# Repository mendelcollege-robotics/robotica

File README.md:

# About
This is the repository for all the files associated with, and used to create, a soccer robot for participation in the [Robocup](https://www.robocup.org/leagues/18). Made by students of the Mendelcollege, from team 'Mendel'.

# Info:

  [Mendelcollege.nl](https://mendelcollege.nl/ontdek-je-talenten/robotica-en-beta/)

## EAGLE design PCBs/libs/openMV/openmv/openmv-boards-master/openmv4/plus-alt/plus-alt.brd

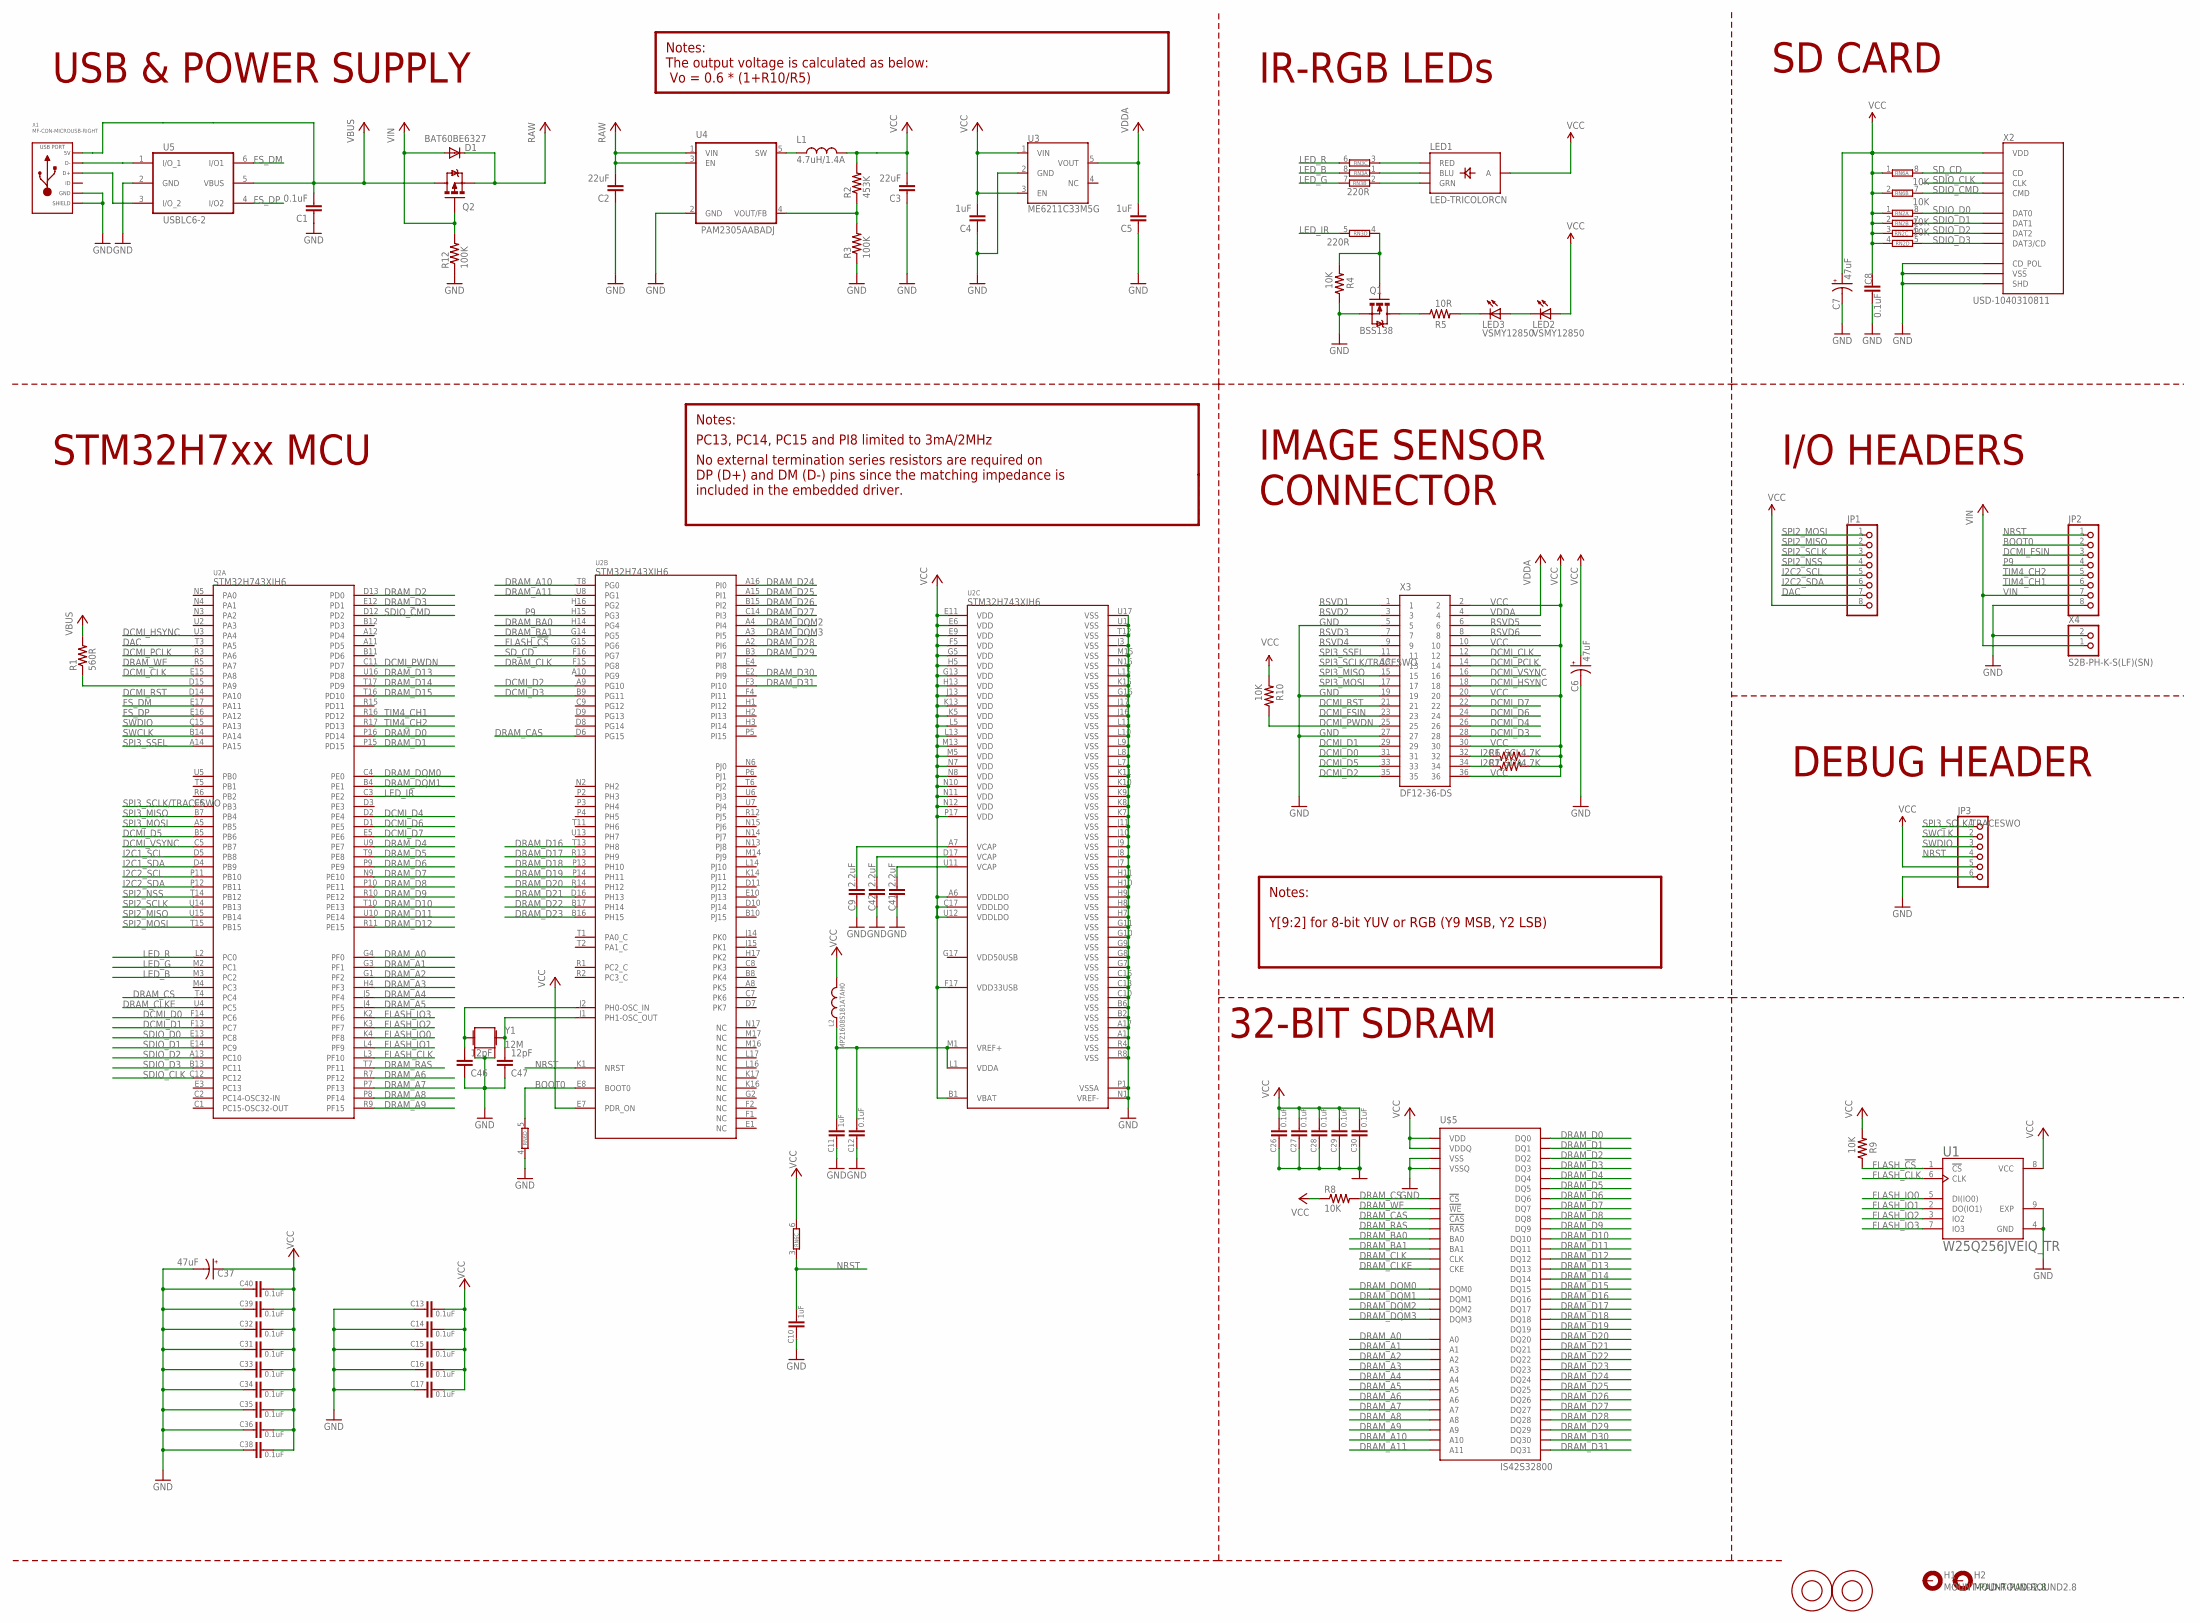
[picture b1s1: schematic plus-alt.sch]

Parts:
C1, C8, C12, C13, C14, C15, C16, C17, C26, C27, C28, C29, C30, C31, C32, C33, C34, C35, C36, C38, C39, C40: 0.1uF; 0402-CAP
C2, C3: 22uF; 0805
C4, C5, C10, C11: 1uF; 0402-CAP
C6, C7, C37: 47uF; EIA3216
C9, C41, C42: 2.2uF; 0402-CAP
C46, C47: 12pF; 0402-CAP
D1: BAT60BE6327; SOD-323
H1, H2: MOUNT-PAD-ROUND2.8; 2,8-PAD
JP1, JP2: PINHD-1X8; 1X08
JP3: PINHD-1X6; 1X06
L1: 4.7uH/1.4A; 1007
L2: MPZ1608S181ATAH0; C0402
LED1: LED-TRICOLORCN; LED-TRICOLOR-SMD
LED2, LED3: VSMY12850; LED-1206
M1, M2: 9774030243R; 9774030151R
Q1: BSS138; SOT23-3
Q2: AO3401; SOT23-3
R1: 560R; 0402-RES
R2: 453K; 0402-RES
R3, R12: 100K; 0402-RES
R4, R8, R9, R10: 10K; 0402-RES
R5: 10R; 0402-RES
R6, R7: 4.7K; 0402-RES
RN2, RN6: 10K; EXBV8V
RN3: 220R; EXBV8V
U1: W25Q256JVEIQ_TR; SON127P800X600X80-9N
U2: *; TFBGA240+25
U3: ME6211C33M5G; SOT23-5
U4: PAM2305AABADJ; TSOT25
U5: USBLC6-2; SOT-23-6L
U$5: IS42S32800; BGA90
X1: MF-CON-MICROUSB-RIGHT; MICROUSB-RIGHT
X2: USD-1040310811; 1040310811
X3: DF12-36-DS
X4: S2B-PH-K-S(LF)(SN); JST-PH-2-THM-RA
Y1: 12M; CRYSTAL-2.5X2.0

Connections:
BOOT0: JP2.2, RN6.5 (2), U2.E8 (BOOT0)
DAC: JP1.7, U2.T3 (PA5)
DCMI_CLK: U2.E15 (PA8), X3.12
DCMI_D0: U2.F14 (PC6), X3.31
DCMI_D1: U2.F13 (PC7), X3.29
DCMI_D2: U2.A9 (PG10), X3.35
DCMI_D3: U2.B9 (PG11), X3.28
DCMI_D4: U2.D2 (PE4), X3.26
DCMI_D5: U2.B5 (PB6), X3.33
DCMI_D6: U2.D1 (PE5), X3.24
DCMI_D7: U2.E5 (PE6), X3.22
DCMI_FSIN: JP2.3, X3.23
DCMI_HSYNC: U2.U3 (PA4), X3.18
DCMI_PCLK: U2.R3 (PA6), X3.14
DCMI_PWDN: R10.1, U2.C11 (PD7), X3.25
DCMI_RST: U2.D14 (PA10), X3.21
DCMI_VSYNC: U2.C5 (PB7), X3.16
DRAM_A0: U2.G4 (PF0), U$5.G8 (A0)
DRAM_A1: U2.G3 (PF1), U$5.G9 (A1)
DRAM_A2: U2.G1 (PF2), U$5.F7 (A2)
DRAM_A3: U2.H4 (PF3), U$5.F3 (A3)
DRAM_A4: U2.J5 (PF4), U$5.G1 (A4)
DRAM_A5: U2.J4 (PF5), U$5.G2 (A5)
DRAM_A6: U2.R7 (PF12), U$5.G3 (A6)
DRAM_A7: U2.P7 (PF13), U$5.H1 (A7)
DRAM_A8: U2.P8 (PF14), U$5.H2 (A8)
DRAM_A9: U2.R9 (PF15), U$5.J3 (A9)
DRAM_A10: U2.T8 (PG0), U$5.G7 (A10)
DRAM_A11: U2.U8 (PG1), U$5.H9 (A11)
DRAM_BA0: U2.H14 (PG4), U$5.J7 (BA0)
DRAM_BA1: U2.G14 (PG5), U$5.H8 (BA1)
DRAM_CAS: U2.D6 (PG15), U$5.K7 (!CAS)
DRAM_CLK: U2.F15 (PG8), U$5.J1 (CLK)
DRAM_CLKE: U2.U4 (PC5), U$5.J2 (CKE)
DRAM_CS: R8.2, U2.T4 (PC4), U$5.J8 (!CS)
DRAM_D0: U2.P16 (PD14), U$5.R8 (DQ0)
DRAM_D1: U2.P15 (PD15), U$5.N7 (DQ1)
DRAM_D2: U2.D13 (PD0), U$5.R9 (DQ2)
DRAM_D3: U2.E12 (PD1), U$5.N8 (DQ3)
DRAM_D4: U2.U9 (PE7), U$5.P9 (DQ4)
DRAM_D5: U2.T9 (PE8), U$5.M8 (DQ5)
DRAM_D6: U2.P9 (PE9), U$5.M7 (DQ6)
DRAM_D7: U2.N9 (PE10), U$5.L8 (DQ7)
DRAM_D8: U2.P10 (PE11), U$5.L2 (DQ8)
DRAM_D9: U2.R10 (PE12), U$5.M3 (DQ9)
DRAM_D10: U2.T10 (PE13), U$5.M2 (DQ10)
DRAM_D11: U2.U10 (PE14), U$5.P1 (DQ11)
DRAM_D12: U2.R11 (PE15), U$5.N2 (DQ12)
DRAM_D13: U2.U16 (PD8), U$5.R1 (DQ13)
DRAM_D14: U2.T17 (PD9), U$5.N3 (DQ14)
DRAM_D15: U2.T16 (PD10), U$5.R2 (DQ15)
DRAM_D16: U2.T13 (PH8), U$5.E8 (DQ16)
DRAM_D17: U2.R13 (PH9), U$5.D7 (DQ17)
DRAM_D18: U2.P13 (PH10), U$5.D8 (DQ18)
DRAM_D19: U2.P14 (PH11), U$5.B9 (DQ19)
DRAM_D20: U2.R14 (PH12), U$5.C8 (DQ20)
DRAM_D21: U2.D16 (PH13), U$5.A9 (DQ21)
DRAM_D22: U2.B17 (PH14), U$5.C7 (DQ22)
DRAM_D23: U2.B16 (PH15), U$5.A8 (DQ23)
DRAM_D24: U2.A16 (PI0), U$5.A2 (DQ24)
DRAM_D25: U2.A15 (PI1), U$5.C3 (DQ25)
DRAM_D26: U2.B15 (PI2), U$5.A1 (DQ26)
DRAM_D27: U2.C14 (PI3), U$5.C2 (DQ27)
DRAM_D28: U2.A2 (PI6), U$5.B1 (DQ28)
DRAM_D29: U2.B3 (PI7), U$5.D2 (DQ29)
DRAM_D30: U2.E2 (PI9), U$5.D3 (DQ30)
DRAM_D31: U2.F3 (PI10), U$5.E2 (DQ31)
DRAM_DQM0: U2.C4 (PE0), U$5.K9 (DQM0)
DRAM_DQM1: U2.B4 (PE1), U$5.K1 (DQM1)
DRAM_DQM2: U2.A4 (PI4), U$5.F8 (DQM2)
DRAM_DQM3: U2.A3 (PI5), U$5.F2 (DQM3)
DRAM_RAS: U2.T7 (PF11), U$5.J9 (!RAS)
DRAM_WE: U2.R5 (PA7), U$5.K8 (!WE)
FLASH_!CS: R9.1, U1.1 (!CS), U2.G15 (PG6)
FLASH_CLK: U1.6 (CLK), U2.L3 (PF10)
FLASH_IO0: U1.5 (DI(IO0)), U2.K4 (PF8)
FLASH_IO1: U1.2 (DO(IO1)), U2.L4 (PF9)
FLASH_IO2: U1.3 (IO2), U2.K3 (PF7)
FLASH_IO3: U1.7 (IO3), U2.K2 (PF6)
FS_DM: U2.E17 (PA11), U5.6 (I/O1)
FS_DP: U2.E16 (PA12), U5.4 (I/O2)
GND: C1.1, C2.1, C3.1, C4.1, C5.1, C6.C (-), C7.C (-), C8.2, C9.2, C10.2, C11.2, C12.2, C13.2, C14.2, C15.2, C16.2, C17.2, C26.2, C27.2, C28.2, C29.2, C30.2, C31.2, C32.2, C33.2, C34.2, C35.2, C36.2, C37.C (-), C38.2, C39.2, C40.2, C41.2, C42.2, C46.1, C47.1, JP2.8, JP3.6, Q1.2 (S), R3.1, R4.1, R12.1, RN6.4 (1), U1.4 (GND), U1.9 (EXP), U2.A1 (VSS), U2.A17 (VSS), U2.B2 (VSS), U2.B6 (VSS), U2.C10 (VSS), U2.C13 (VSS), U2.C16 (VSS), U2.G7 (VSS), U2.G8 (VSS), U2.G9 (VSS), U2.G10 (VSS), U2.G11 (VSS), U2.G16 (VSS), U2.H7 (VSS), U2.H8 (VSS), U2.H9 (VSS), U2.H10 (VSS), U2.H11 (VSS), U2.J3 (VSS), U2.J7 (VSS), U2.J8 (VSS), U2.J9 (VSS), U2.J10 (VSS), U2.J11 (VSS), U2.J16 (VSS), U2.J17 (VSS), U2.K7 (VSS), U2.K8 (VSS), U2.K9 (VSS), U2.K10 (VSS), U2.K11 (VSS), U2.K15 (VSS), U2.L7 (VSS), U2.L8 (VSS), U2.L9 (VSS), U2.L10 (VSS), U2.L11 (VSS), U2.L15 (VSS), U2.M15 (VSS), U2.N1 (VREF-), U2.N16 (VSS), U2.P1 (VSSA), U2.R4 (VSS), U2.R8 (VSS), U2.T12 (VSS), U2.U1 (VSS), U2.U17 (VSS), U3.2 (GND), U4.2 (GND), U5.2 (GND), U$5.A3 (VSS), U$5.B3 (VSSQ), U$5.B8 (VSSQ), U$5.C1 (VSSQ), U$5.D1 (VSSQ), U$5.E9 (VSSQ), U$5.F1 (VSS), U$5.L3 (VSS), U$5.L9 (VSSQ), U$5.M1 (VSSQ), U$5.N1 (VSSQ), U$5.P3 (VSSQ), U$5.P8 (VSSQ), U$5.R3 (VSS), X1.5 (GND), X1.S1 (SLD), X1.S2 (SLD), X1.S3 (SLD), X1.S4 (SLD), X1.S5 (SLD), X1.S6 (SLD), X2.CD$2 (CD_POL), X2.G$1 (SHD), X2.G$2 (SHD), X2.G$3 (SHD), X2.G$4 (SHD), X2.P$6 (VSS), X3.5, X3.19, X3.27, X4.2 (1), Y1.2, Y1.4
I2C1_SCL: R6.2, U2.D5 (PB8), X3.32
I2C1_SDA: R7.2, U2.D4 (PB9), X3.34
I2C2_SCL: JP1.5, U2.P11 (PB10)
I2C2_SDA: JP1.6, U2.P12 (PB11)
LED_B: RN3.8 (2), U2.M3 (PC2)
LED_G: RN3.7 (2), U2.M2 (PC1)
LED_IR: RN3.5 (2), U2.C3 (PE2)
LED_R: RN3.6 (2), U2.L2 (PC0)
unnamed: U5.1 (I/O_1), X1.2 (D-)
unnamed: U5.3 (I/O_2), X1.3 (D+)
unnamed: Q1.1 (G), R4.2, RN3.4 (1)
unnamed: LED1.B (BLU), RN3.1
unnamed: LED1.R (RED), RN3.3 (1)
unnamed: LED1.G (GRN), RN3.2 (1)
unnamed: LED3.C, R5.2
unnamed: R2.1, R3.2, U4.4 (VOUT/FB)
unnamed: Q1.3 (D), R5.1
unnamed: LED2.C, LED3.A
unnamed: C11.1, C12.1, L2.1, U2.L1 (VDDA), U2.M1 (VREF+)
unnamed: R1.1, U2.D15 (PA9)
unnamed: C46.2, U2.J2 (PH0-OSC_IN), Y1.3 (2)
unnamed: C47.2, U2.J1 (PH1-OSC_OUT), Y1.1
NRST: C10.1, JP2.1, JP3.4, RN6.3 (1), U2.K1 (NRST)
P9: JP2.4, U2.H15 (PG3)
RAW: C2.2, D1.1 (C), Q2.2 (S), U4.1 (VIN), U4.3 (EN)
RSVD1: X3.1
RSVD2: X3.3
RSVD3: X3.7
RSVD4: X3.9
RSVD5: X3.6
RSVD6: X3.8
SDIO_CLK: U2.C12, X2.P$5 (CLK)
SDIO_CMD: RN6.7 (2), U2.D12 (PD2), X2.P$3 (CMD)
SDIO_D0: RN2.8 (2), U2.E13 (PC8), X2.P$7 (DAT0)
SDIO_D1: RN2.7 (2), U2.E14 (PC9), X2.P$8 (DAT1)
SDIO_D2: RN2.6 (2), U2.A13 (PC10), X2.P$1 (DAT2)
SDIO_D3: RN2.5 (2), U2.B13 (PC11), X2.P$2 (DAT3/CD)
SD_CD: RN6.8 (2), U2.F16 (PG7), X2.CD$1 (CD)
SPI2_MISO: JP1.2, U2.U15 (PB14)
SPI2_MOSI: JP1.1, U2.T15 (PB15)
SPI2_NSS: JP1.4, U2.T14 (PB12)
SPI2_SCLK: JP1.3, U2.U14 (PB13)
SPI3_MISO: U2.B7 (PB4), X3.15
SPI3_MOSI: U2.A5 (PB5), X3.17
SPI3_SCLK/TRACESWO: JP3.1, U2.C6 (PB3), X3.13
SPI3_SSEL: U2.A14 (PA15), X3.11
SW: L1.1, U4.5 (SW)
SWCLK: JP3.2, U2.B14 (PA14)
SWDIO: JP3.3, U2.C15 (PA13)
TIM4_CH1: JP2.6, U2.R16 (PD12)
TIM4_CH2: JP2.5, U2.R17 (PD13)
VBUS: C1.2, Q2.3 (D), R1.2, U5.5 (VBUS), X1.1 (5V)
VCAP1: C9.1, U2.A7 (VCAP)
VCAP3: C41.1, U2.U11 (VCAP)
VCAP4: C42.1, U2.D17 (VCAP)
VCC: C3.2, C4.2, C6.A (+), C7.A (+), C8.1, C13.1, C14.1, C15.1, C16.1, C17.1, C26.1, C27.1, C28.1, C29.1, C30.1, C31.1, C32.1, C33.1, C34.1, C35.1, C36.1, C37.A (+), C38.1, C39.1, C40.1, JP1.8, JP3.5, L1.2, L2.2, LED1.V (A), LED2.A, R2.2, R6.1, R7.1, R8.1, R9.2, R10.2, RN2.1, RN2.2 (1), RN2.3 (1), RN2.4 (1), RN6.1, RN6.2 (1), RN6.6 (2), U1.8 (VCC), U2.A6 (VDDLDO), U2.B1 (VBAT), U2.C17 (VDDLDO), U2.E6 (VDD), U2.E7 (PDR_ON), U2.E9 (VDD), U2.E11 (VDD), U2.F5 (VDD), U2.F17 (VDD33USB), U2.G5 (VDD), U2.G13 (VDD), U2.H5 (VDD), U2.H13 (VDD), U2.J13 (VDD), U2.K5 (VDD), U2.K13 (VDD), U2.L5 (VDD), U2.L13 (VDD), U2.M5 (VDD), U2.M13 (VDD), U2.N7 (VDD), U2.N8 (VDD), U2.N10 (VDD), U2.N11 (VDD), U2.N12 (VDD), U2.P17 (VDD), U2.U12 (VDDLDO), U3.1 (VIN), U3.3 (EN), U$5.A7 (VDD), U$5.B2 (VDDQ), U$5.B7 (VDDQ), U$5.C9 (VDDQ), U$5.D9 (VDDQ), U$5.E1 (VDDQ), U$5.F9 (VDD), U$5.L1 (VDDQ), U$5.L7 (VDD), U$5.M9 (VDDQ), U$5.N9 (VDDQ), U$5.P2 (VDDQ), U$5.P7 (VDDQ), U$5.R7 (VDD), X2.P$4 (VDD), X3.2, X3.10, X3.20, X3.30, X3.36
VDDA: C5.2, U3.5 (VOUT), X3.4
VIN: D1.2 (A), JP2.7, Q2.1 (G), R12.2, X4.1 (2)

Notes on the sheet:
PC13, PC14, PC15 and PI8 limited to 3mA/2MHz
SD CARD
Y[9:2] for 8-bit YUV or RGB (Y9 MSB, Y2 LSB)
Notes:
IMAGE SENSOR CONNECTOR
STM32H7xx MCU
IR-RGB LEDs
USB & POWER SUPPLY
DEBUG HEADER
I/O HEADERS
No external termination series resistors are required on DP (D+) and DM (D-) pins since the matching impedance is included in the embedded driver.
The output voltage is calculated as below: Vo = 0.6 * (1+R10/R5)
32-BIT SDRAM

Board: 6 copper layers, 80 parts (25 on the bottom side), 134 nets, no tracks yet.

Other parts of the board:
U$1: WEEE
U$2: ROHS
U$3: OMV-LOGO
U$4: OMV-LOGO-SMALL

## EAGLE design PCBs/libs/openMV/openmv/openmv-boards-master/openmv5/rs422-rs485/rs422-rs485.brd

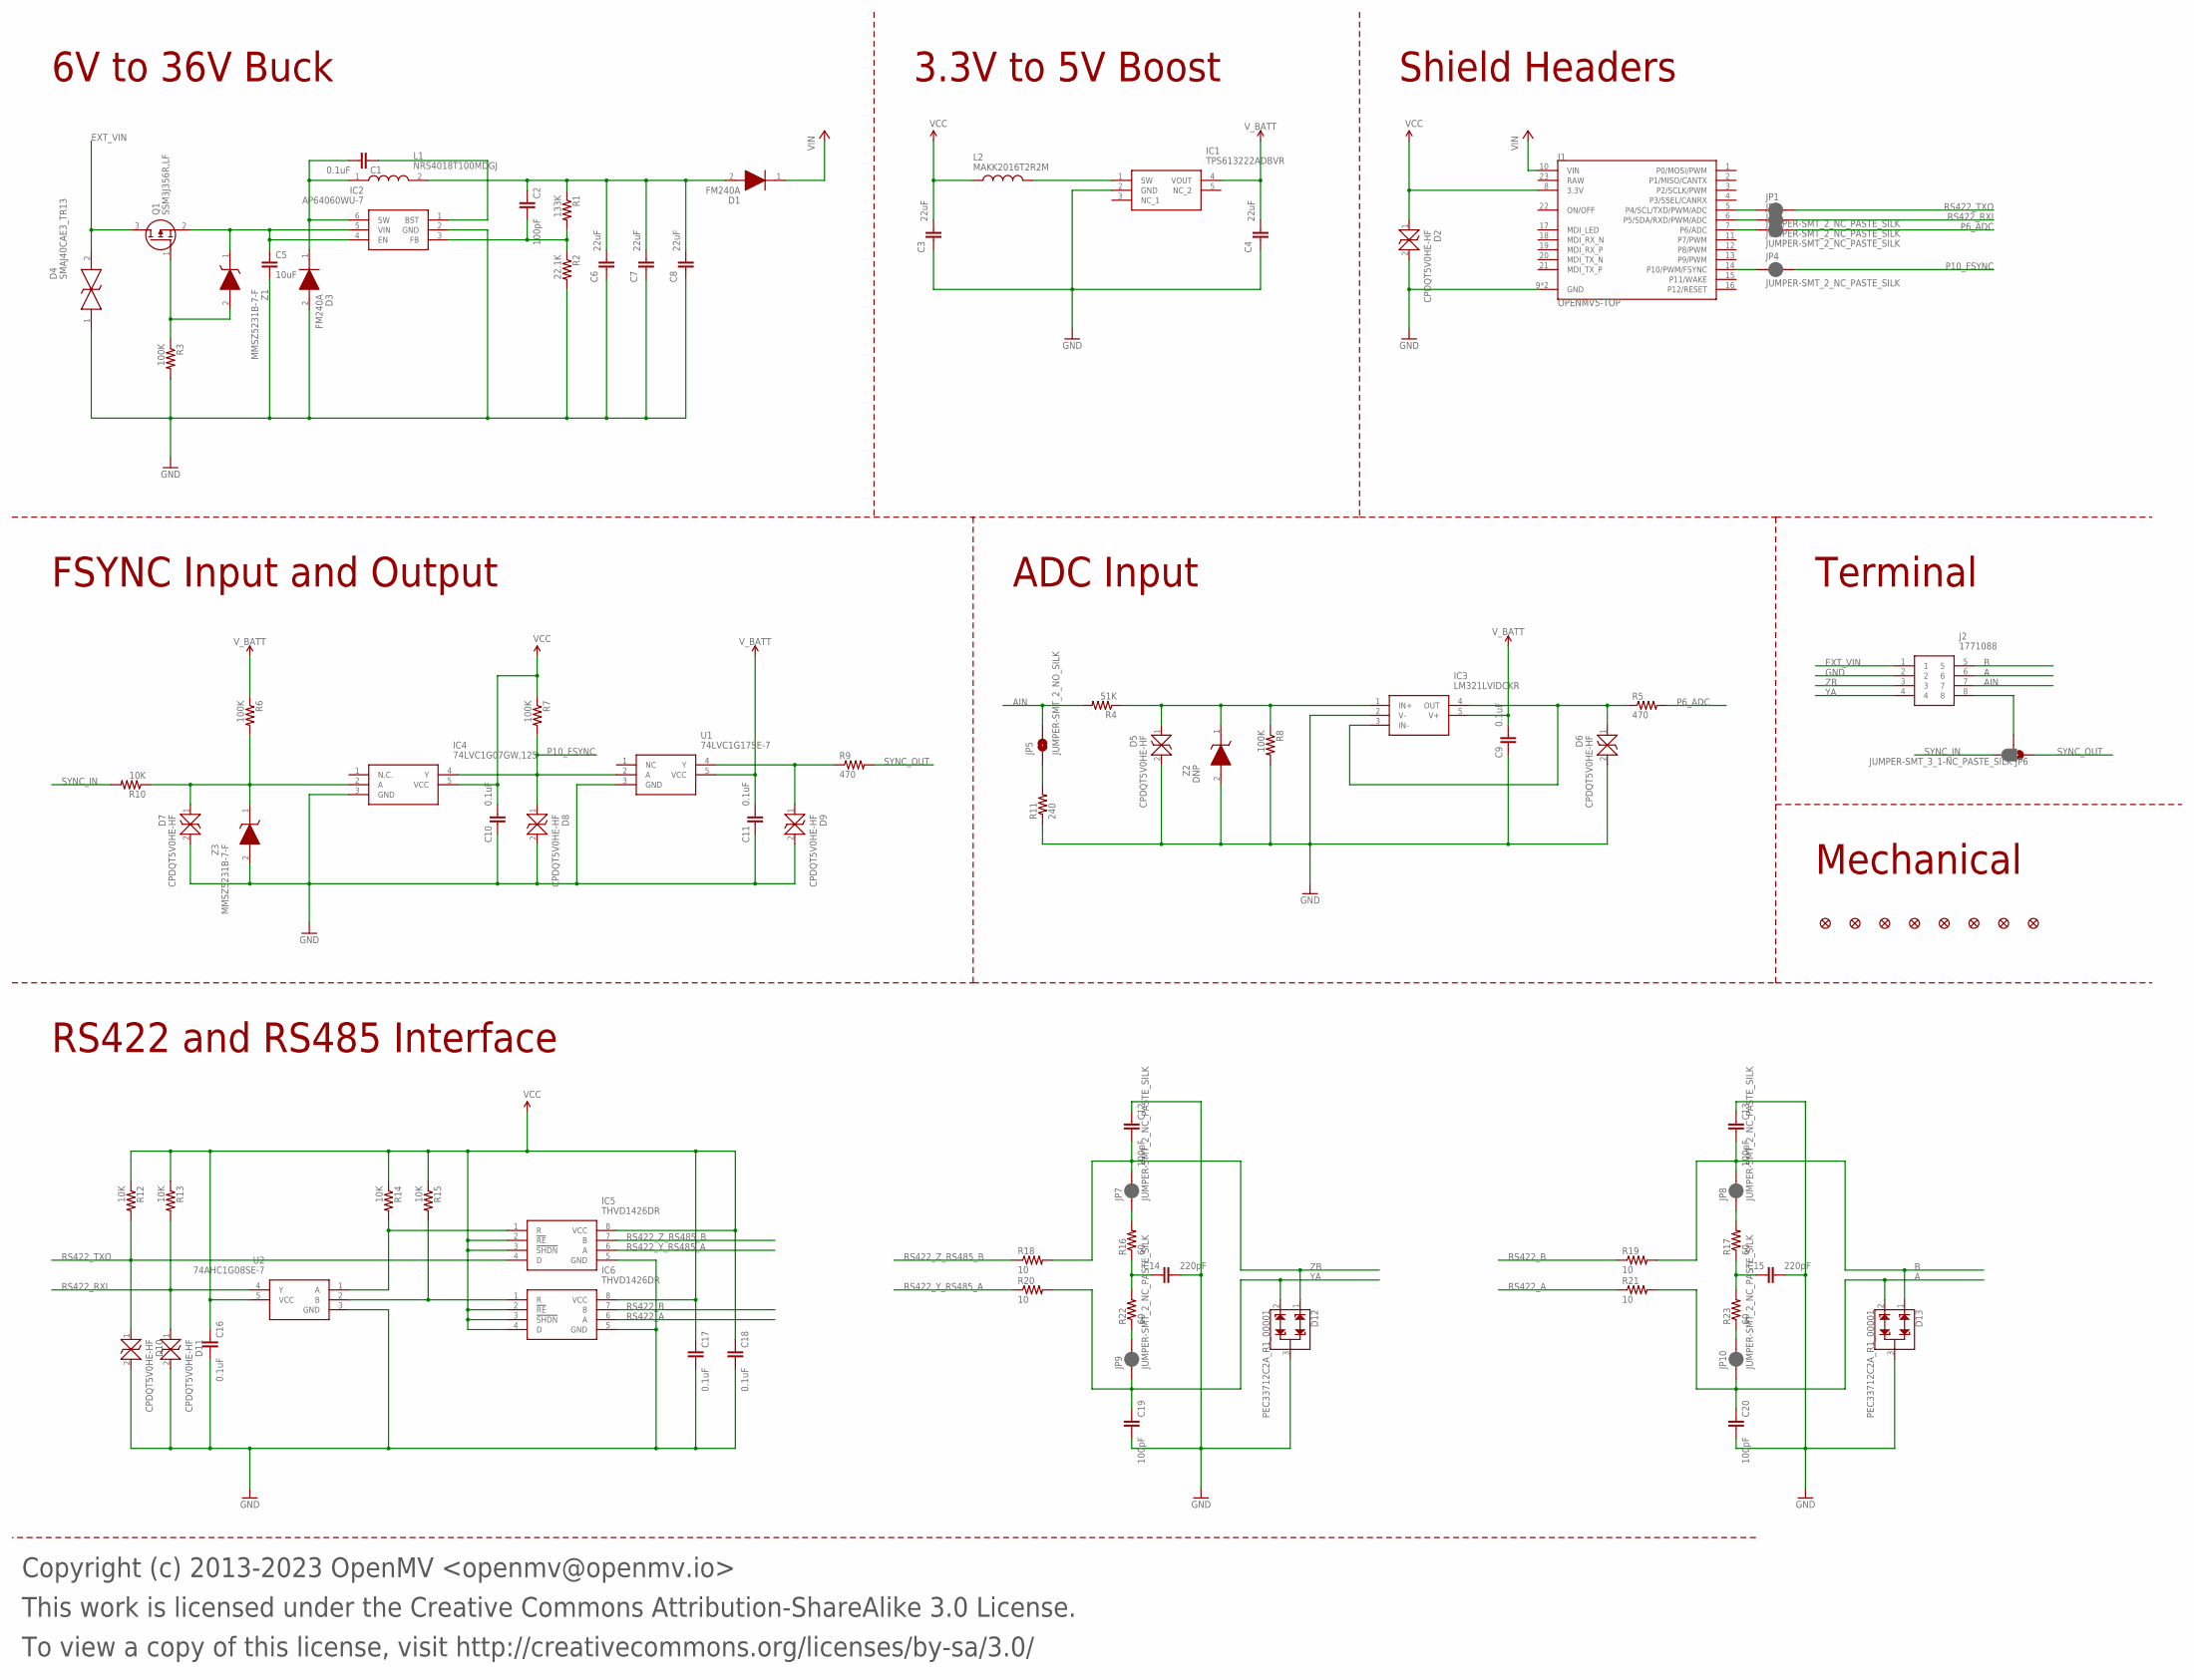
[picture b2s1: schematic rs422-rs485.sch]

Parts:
C1, C9, C10, C11, C16, C17, C18: 0.1uF; 0402-CAP; MPN GRM155R71H104KE14D
C2, C12, C13, C19, C20: 100pF; 0402-CAP; MPN CC0402JRNPO9BN101
C3, C4, C6, C7, C8: 22uF; 0805; MPN CL21A226MQQNNNE
C5: 10uF; C0805; MPN GRM21BR61H106KE43K
C14, C15: 220pF; 0402-CAP; MPN 0402B221K500CT
D1, D3: FM240A; DIOM5025X231N; MPN FM240A
D2, D5, D6, D7, D8, D9, D10, D11: CPDQT5V0HE-HF; CPDQT5V0HEHF; MPN CPDQT5V0HE-HF
D4: SMAJ40CAE3_TR13; SMAJ40CAE3TR13; MPN SMAJ40CAe3/TR13
D12, D13: PEC33712C2A_R1_00001; SOT23-3; MPN PEC33712C2A_R1_00001
FD1, FD2, FD3, FD4, FD5, FD6, FD7, FD8: FIDUCIAL1X2; FIDUCIAL-1X2
IC1: TPS613222ADBVR; SOT95P280X145-5N; MPN TPS613222ADBVR
IC2: AP64060WU-7; SOT95P280X100-6N; MPN AP64060WU-7
IC3: LM321LVIDCKR; SOT65P210X110-5N; MPN LM321LVIDCKR
IC4: 74LVC1G07GW,125; SOT65P212X110-5N; MPN 74LVC1G07GW,125
IC5, IC6: THVD1426DR; SOIC127P600X175-8N; MPN THVD1426DR
J1: OPENMV5-TOP
J2: 1771088; MPN 1771088
JP1, JP2, JP3, JP4, JP7, JP8, JP9, JP10: JUMPER-SMT_2_NC_PASTE_SILK; SMT-JUMPER_2_NC_PASTE_SILK
JP5: JUMPER-SMT_2_NO_SILK; SMT-JUMPER_2_NO_SILK
JP6: JUMPER-SMT_3_1-NC_PASTE_SILK; SMT-JUMPER_3_1-NC_PASTE_SILK
L1: NRS4018T100MDGJ; MPN NRS4018T100MDGJ
L2: MAKK2016T2R2M; INDC2016X100N; MPN MAKK2016T2R2M
Q1: SSM3J356R,LF; SOTFL95P240X88-3N; MPN SSM3J356R,LF
R1: 133K; 0402-RES; MPN RC0402FR-07133KL
R2: 22.1K; 0402-RES; MPN CR0402-FX-2212GLF
R3, R6, R7, R8: 100K; 0402-RES; MPN AC0402FR-07100KL
R4: 51K; 0402-RES; MPN RC0402JR-0751KL
R5, R9: 470; R0603; MPN CR0603-FX-4700ELF
R10, R12, R13, R14, R15: 10K; 0402-RES; MPN AC0402FR-1310KL
R11: 240; R0603; MPN RK73B1JTTD241J
R16, R17, R22, R23: 60; R1206; MPN RC1206FR-0760R4L
R18, R19, R20, R21: 10; R0805; MPN RK73B2ATTD100J
U1: 74LVC1G17SE-7; SOT65P210X110-5N; MPN 74LVC1G17SE-7
U2: 74AHC1G08SE-7; SOT65P210X110-5N; MPN 74AHC1G08SE-7
Z1, Z3: MMSZ5231B-7-F; SOD3716X145N; MPN MMSZ5231B-7-F
Z2: DNP; SOD2512X110N; MPN MM3Z3V6T1G

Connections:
A: C20.1, D13.2, J2.6, JP10.1, R21.2
AIN: J2.7, JP5.2, R4.2
AIN_INT: D5.1, IC3.1 (IN+), R4.1, R8.1, Z2.1 (K)
AIN_OUT: D6.1, IC3.3 (IN-), IC3.4 (OUT), R5.1
AIN_S: JP5.1, R11.2
A_J: JP10.2, R23.1
B: C13.2, D13.1, J2.5, JP8.2, R19.2
B_J: JP8.1, R17.2
EXT_VIN: D4.2, J2.1, Q1.3 (D)
EXT_VIN_BST: C1.1, IC2.1 (BST)
EXT_VIN_FB: C2.2, IC2.3 (FB), R1.2, R2.1
EXT_VIN_G: Q1.1 (G), R3.1, Z1.2 (A)
EXT_VIN_INT: C5.1, IC2.4 (EN), IC2.5 (VIN), Q1.2 (S), Z1.1 (K)
EXT_VIN_OUT: C2.1, C6.2, C7.2, C8.2, D1.2 (A), L1.2, R1.1
EXT_VIN_SW: C1.2, D3.1 (K), IC2.6 (SW), L1.1
GND: C3.1, C4.1, C5.2, C6.1, C7.1, C8.1, C9.1, C10.1, C11.1, C12.1, C13.1, C14.2, C15.2, C16.2, C17.2, C18.2, C19.2, C20.2, D2.2, D3.2 (A), D4.1, D5.2, D6.2, D7.2, D8.2, D9.2, D10.2, D11.2, D12.3, D13.3, IC1.2 (GND), IC2.2 (GND), IC3.2 (V-), IC4.3 (GND), IC5.5 (GND), IC6.5 (GND), J1.9 (GND), J1.24 (GND), J2.2, R2.2, R3.2, R8.2, R11.1, U1.3 (GND), U2.3 (GND), Z2.2 (A), Z3.2 (A)
P6_ADC: JP3.2, R5.2
P6_ADC_INT: J1.7 (P6/ADC), JP3.1
P10_FSYNC: D8.1, IC4.4 (Y), JP4.2, R7.2, U1.2 (A)
P10_FSYNC_INT: J1.14 (P10/PWM/FSYNC), JP4.1
RA: IC5.1 (R), R14.2, U2.1 (A)
RB: IC6.1 (R), R15.2, U2.2 (B)
RS232_RXI_INT: J1.6 (P5/SDA/RXD/PWM/ADC), JP2.1
RS232_TXO_INT: J1.5 (P4/SCL/TXD/PWM/ADC), JP1.1
RS422_A: IC6.6 (A), R21.1
RS422_B: IC6.7 (B), R19.1
RS422_RXI: D11.1, JP2.2, R13.2, U2.4 (Y)
RS422_S: C15.1, R17.1, R23.2
RS422_TXO: D10.1, IC5.4 (D), JP1.2, R12.2
RS422_Y_RS485_A: IC5.6 (A), R20.1
RS422_Z_RS485_B: IC5.7 (B), R18.1
RS485_S: C14.1, R16.1, R22.2
SW: IC1.1 (SW), L2.2
SYNC: J2.8, JP6.2
SYNC_IN: JP6.3, R10.2
SYNC_IN_INT: D7.1, IC4.2 (A), R6.2, R10.1, Z3.1 (K)
SYNC_OUT: JP6.1, R9.2
SYNC_OUT_INT: D9.1, R9.1, U1.4 (Y)
VCC: C3.2, C10.2, C16.1, C17.1, C18.1, D2.1, IC4.5 (VCC), IC5.2 (!RE), IC5.3 (!SHDN), IC5.8 (VCC), IC6.2 (!RE), IC6.3 (!SHDN), IC6.4 (D), IC6.8 (VCC), J1.8 (3.3V), L2.1, R7.1, R12.1, R13.1, R14.1, R15.1, U2.5 (VCC)
VIN: D1.1 (K), J1.10 (VIN)
V_BATT: C4.2, C9.2, C11.2, IC1.4 (VOUT), IC3.5 (V+), R6.1, U1.5 (VCC)
YA: C19.1, D12.2, J2.4, JP9.1, R20.2
YA_J: JP9.2, R22.1
YB_J: JP7.1, R16.2
ZB: C12.2, D12.1, J2.3, JP7.2, R18.2

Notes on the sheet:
Copyright (c) 2013-2023 OpenMV <openmv@openmv.io>
This work is licensed under the Creative Commons Attribution-ShareAlike 3.0 License.
To view a copy of this license, visit http://creativecommons.org/licenses/by-sa/3.0/
FSYNC Input and Output
Mechanical
Shield Headers
6V to 36V Buck
3.3V to 5V Boost
RS422 and RS485 Interface
Terminal
ADC Input

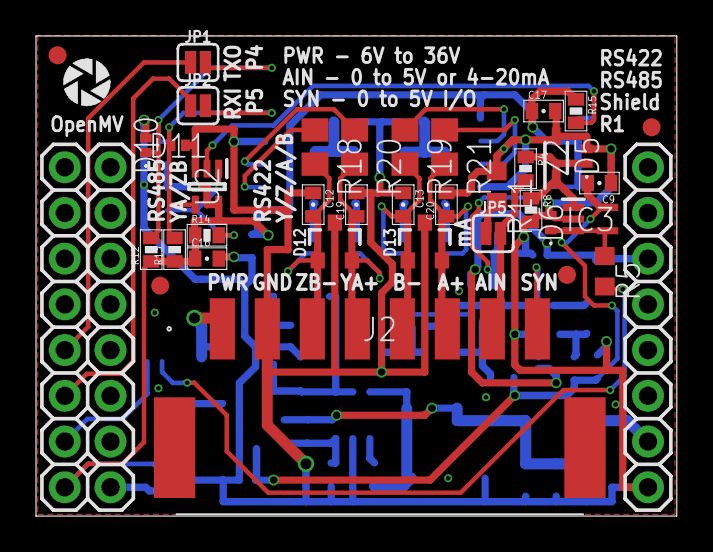
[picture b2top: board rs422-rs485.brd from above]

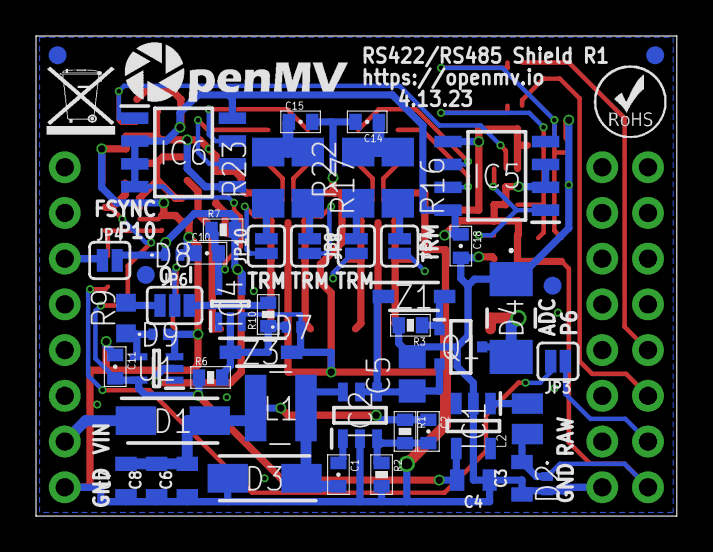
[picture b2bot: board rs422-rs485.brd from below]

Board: 2 copper layers, 35.6 x 26.7 mm, 94 parts (56 on the bottom side), 45 nets.

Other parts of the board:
U$1: WEEE
U$2: ROHS
U$3: OMV-LOGO
U$9: OPENMV-LOGO

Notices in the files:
PCBs/libs/openMV/openmv/openmv-boards-master/openmv4/sensors/MT9V024/MT9V024.sch:
Copyright (c) 2018 OpenMV
parts and their libraries:
SparkFun-Connectors: Licensing: Creative Commons ShareAlike 4.0 International - https://creativecommons.org/licenses/by-sa/4.0
sfe: Licensing: CC v3.0 Share-Alike You are welcome to use this library for commercial purposes.
